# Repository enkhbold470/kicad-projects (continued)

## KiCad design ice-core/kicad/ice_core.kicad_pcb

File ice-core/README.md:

# Ice Core

A 6-layer iCE40UP5K FPGA board with 8 MB PSRAM and three Pmods, programmed and clocked over USB-C by an RP2040.

| Layers | Size | Parts | Nets | Connections routed | Vias | ERC errors | DRC errors / unconnected / parity |
|---|---|---|---|---|---|---|---|
| 6 | 80 x 60 mm | 78 | 73 | 234 -> 0 open | 180 | 0 | 0 / 0 / 0 |

**Not fabricated, assembled or powered.** Every number on this page is measured by KiCad 10 on the files in this folder; the full measurements are in [`report.json`](report.json).

| | |
|---|---|
| KiCad project | [`kicad/`](kicad/) |
| Gerbers, BOM, CPL, STEP, schematic PDF | [`fab/`](fab/) |
| Renders | [top](media/top.png), [bottom](media/bottom.png) |
| Design process, every step as KiCad rendered it | [`media/design-process.mp4`](media/design-process.mp4) |

Ice Core is an FPGA board: a Lattice iCE40UP5K with 8 MB of QSPI PSRAM and three
Pmod host ports, programmed and clocked over USB-C by an RP2040, on 80 x 60 mm of
6-layer board. It was designed with the HeyPCB method on KiCad 10 (the headless
heypcb-kicad pipeline, routed by Freerouting 2.4.1) from the brief in `board.json`.

**This board has not been fabricated, assembled or powered.** It passes ERC, the
netlist round trip, routing, DRC with schematic parity, DFM and the fab gate in
KiCad 10.0.6, headless, and nothing more. No firmware or gateware for it exists.
Every gate number below is read from `report.json`. The stackup, the vias in the
exposed pads, the pours, part positions, pad nets, via counts and spacing, the
silkscreen and each footprint's 3D model were read from `kicad/ice_core.kicad_pcb`
with KiCad 10.0.6's pcbnew.

## What it is

| | |
|---|---|
| FPGA | Lattice iCE40UP5K-SG48 (QFN-48), booting from a W25Q32JV 4 MB SPI flash in controller mode |
| FPGA memory | AP Memory APS6404L-3SQR-SN, 8 MB QSPI pseudo-SRAM (SOIC-8), on six FPGA I/O |
| MCU | Raspberry Pi RP2040 (QFN-56) with its own W25Q32JV 4 MB QSPI boot flash and the ABM8-272-T3 12 MHz crystal |
| MCU role | USB bridge and FPGA programmer: drives CRESET_B, reads CDONE, owns the configuration SPI, clocks the FPGA from GPOUT0 |
| USB | USB-C receptacle (HRO TYPE-C-31-M-12), 5.1k CC pull-downs, USBLC6-2SC6 ESD clamp, 27 ohm series terminations at the RP2040 |
| 3.3 V | Diodes AP63203WU buck from VBUS, 2 A, 3.9 uH |
| 1.2 V | AP2112K-1.2 LDO from VBUS, so the FPGA core rises before its 3.3 V banks; VCCPLL through a 100 ohm / 4.7 uF / 100 nF filter |
| I/O | three 12-pin Pmod host ports (2x6 right-angle sockets) on the FPGA, 8 signals each |
| UI | common-anode RGB LED on the iCE40's RGB driver; BOOT, RESET (RP2040) and USER (FPGA) buttons; PWR, ACT and DONE LEDs |
| Mechanical | 80 x 60 mm, 2 mm corner radius, four M3 holes (3.2 mm) |
| Stackup | 6 copper layers (below) |

### Connections that firmware and gateware need

RP2040 (pin numbers and names from the KiCad symbol, read back from the run's
netlist):

| RP2040 | pin | net | use |
|---|---|---|---|
| GPIO16 | 27 | CFG_CIPO | SPI0 RX: flash DO and the FPGA's SPI_SI |
| GPIO17 | 28 | CFG_SS | SPI0 CSn: flash /CS and the FPGA's SPI_SS_B (10k pull-up) |
| GPIO18 | 29 | CFG_SCK | SPI0 SCK (10k pull-up) |
| GPIO19 | 30 | CFG_COPI | SPI0 TX: flash DI and the FPGA's SPI_SO |
| GPIO20 | 31 | FPGA_CRESET | CRESET_B (10k pull-up) |
| GPIO21 | 32 | FPGA_CLK | GPOUT0 into the iCE40's global buffer pin 35 (IOT_46b_G0) |
| GPIO22 | 34 | FPGA_CDONE | CDONE (10k pull-up) |
| GPIO24 | 36 | LED_DONE | DONE LED (firmware mirrors CDONE) |
| GPIO25 | 37 | LED_ACT | ACT LED |
| QSPI_* | 51-56 | QSPI_* | boot flash |
| USB_DM / USB_DP | 46 / 47 | via 27 ohm | USB-C |

iCE40UP5K-SG48 (package pin numbers; every one except RGB0-2 is an `IO*` pin of
the KiCad symbol):

| function | pins |
|---|---|
| PSRAM CE#, SCLK, SIO0, SIO1, SIO2, SIO3 | 3, 4, 6, 9, 10, 11 |
| Pmod A pins 1-4 / 7-10 | 2, 47, 45, 43 / 48, 46, 44, 42 |
| Pmod B pins 1-4 / 7-10 | 25, 21, 19, 13 / 26, 23, 20, 18 |
| Pmod C pins 1-4 / 7-10 | 38, 36, 32, 28 / 37, 34, 31, 27 |
| clock in (from RP2040 GPOUT0) | 35 (G0) |
| USER button (to GND, enable the pull-up in gateware) | 12 |
| RGB0 / RGB1 / RGB2 | 39 red / 40 green / 41 blue cathode |
| configuration SPI SO / SCK / SS / SI | 14 / 15 / 16 / 17 |

The pin plan: the symbol has 36 `IO*` pins, 4 of them the configuration SPI, which
leaves 32 general I/O, and this board uses all 32. Each Pmod takes the I/O on the
side of the FPGA it faces and its missing pins from the next corner
counter-clockwise (Pmod B from the bottom of the right side, Pmod C from the right
end of the top, Pmod A from the top of the left side), so no Pmod crosses the
configuration SPI at the bottom-left corner. An earlier plan crossed it with Pmod B
and left PB8 open at pin 11. Pmod order along each connector follows the pin order
along the FPGA's edge.

Pmod pin numbers are Digilent's (Pmod Interface Specification 1.1.0, Figure 5).
On KiCad's `PinSocket_2x06_P2.54mm_Horizontal` they land as Pmod pin 1 -> pad 11,
2 -> 9, 3 -> 7, 4 -> 5, 5 (GND) -> 3, 6 (3V3) -> 1, 7 -> 12, 8 -> 10, 9 -> 8,
10 -> 6, 11 (GND) -> 4, 12 (3V3) -> 2: the footprint's square pad 1 is Pmod pin 6.

## Stackup

pcbnew reads 6 copper layers and a 1.6 mm board from the board file. The file holds
no stackup section, so this is KiCad's default 6-layer stackup, not a fab's: choose
the fab's own 6-layer stackup when ordering. pcbnew's stackup object is not
scriptable in KiCad 10.0.6, so the layer thicknesses below come from the gerber job
file (`ice_core-job.gbrjob` in `fab/ice_core_gerbers.zip`). Nothing on this board
is impedance controlled (USB runs at Full Speed).

| layer | role while routing | pour after routing | filled as | copper |
|---|---|---|---|---|
| F.Cu | signal | GND | 12 pieces | 0.035 mm |
| In1.Cu | GND plane | GND | 1 piece | 0.035 mm |
| In2.Cu | signal | GND | 2 pieces | 0.035 mm |
| In3.Cu | power plane | 3V3, zone priority 1 | 1 piece | 0.035 mm |
| In4.Cu | GND plane | GND | 1 piece | 0.035 mm |
| B.Cu | signal | GND | 1 piece | 0.035 mm |

In3.Cu is `auto` in the brief: the supply rail with at least 1.5x the pins of the
next one. In this run's netlist 3V3 has 54 pins and no other supply more than 12
(VBUS). Five FR4 dielectrics of 0.274 mm, 1.6 mm overall.

Why this plan: every routed layer sits next to a plane (F.Cu over In1, In2 between
In1 and In3, B.Cu over In4), so every signal has its return path beside it, and
In3/In4 are a tightly coupled power/ground pair. Each of the three planes fills as
one piece. The pieces are counted on the fill stored in the board file. The silk
stage removed 8 stitching vias after that fill, and refilling a copy of the board
gave the same counts on every layer. The price is routing room: Freerouting routes
on F.Cu, In2.Cu and B.Cu only, the same three layers as on a 4-layer board.

## Measured gates

One full run with media, 2026-10-01: KiCad 10.0.6 (from the DRC report),
Freerouting 2.4.1 (from its log). The Specctra export carried the brief's 0.5 mm
hole-to-hole minimum to Freerouting as a 0.3 mm `via_via` clearance
(`viaViaClearance_mm` in the report: 0.5 mm + 0.3 mm drill - 0.5 mm via).

| gate | measured |
|---|---|
| Compose | 78 parts, 73 nets, 3 no-connects (J1.A8, J1.B8, U3.4) |
| Part binding | 74 bound, 0 unsourced, 0 conflicts; H1-H4 not in the BOM; 17 Extended part numbers, $51.0 estimated JLC Extended fees |
| ERC | 0 errors, 0 warnings |
| Netlist round trip | identical, 73 nets |
| Route | 234 -> 0 open. Fanout solve kept: 0 open, DRC score 0, 101 vias. Fanout-off solve: 2 open (PSRAM_CS, U4_RP_DM), and the last mile closed neither (U4_RP_DM hit its 400,000-expansion search cap, PSRAM_CS had no path). 2 locked vias in exposed pads (U4.57, U6.49). 839 tracks, 2034.8 mm (F.Cu 1180.9, In2.Cu 644.1, B.Cu 209.8) |
| Pours | GND on F.Cu, B.Cu, In1.Cu, In4.Cu, In2.Cu; 3V3 on In3.Cu; 87 stitching vias, 0 island-repair vias; 0 open after the pours, after stitching and at the end; 188 vias after the pours |
| Silkscreen | 11 of 11 words in place of designators; 55 designators seated, 12 hidden where nothing fit; all 4 title lines placed, on the back; 8 GND stitching vias displaced under text; 90 footprint silk items clipped at the board edge (29 on each Pmod socket J2-J4, 3 on the USB-C J1) |
| DRC (fresh, schematic parity) | 0 errors, 0 unconnected, 0 parity; 4 warnings, all `lib_footprint_mismatch`, on J1-J4, the four footprints whose silk was clipped; no repairs |
| DFM (`jlcpcb_6layer`) | 0 errors, 1 warning: stock footprint silk down to 0.10 mm (292 items), printed at the fab's 0.15 mm |
| Fab | ready, no blockers; 6 copper gerbers (F, In1, In2, In3, In4, B) and a gerber job with LayerNumber 6 and a 1.6 mm board; drill, BOM, CPL (6 rotations corrected), schematic PDF, STEP |
| Media | all ran: 63 3D frames, then the raytraced renders and the design-process video (216 frames; 150.0 s at 1920 x 1080, measured with ffprobe) |

Vias, measured on the finished board: 180 in all. 101 are routed vias at 0.5/0.3 mm,
2 of them the locked vias in the exposed pads. 79 are stitching vias at 0.6/0.3 mm:
87 laid by the pour stage, less the 8 the silkscreen displaced. The closest two via
holes are 0.507 mm apart (PB10 and PB3), and no pair is under the 0.5 mm minimum.
DRC reports no `hole_to_hole` rows.

## Silkscreen

The front carries a word instead of a designator on the 11 parts a user plugs into,
presses or reads: USB, PMOD A, PMOD B, PMOD C, BOOT, RST, USER, PWR, ACT, DONE and
RGB.

The board's name is on the back: all four title lines ("Ice Core", "iCE40UP5K +
RP2040, 6 layers", "rev A  heypcb-kicad", "pure KiCad 10 + Freerouting"), placed as
one block. The brief asks for the block on the board's centre line, 22 mm from the
top edge. That spot was not free, so the block landed 9 mm left and 3 mm down, at
x 19.9-42.1 mm and y 23.5-32.9 mm from the board's top-left corner, behind the
RP2040's right side and the PSRAM. The previous full run, the one this README
described before, placed none of the four lines, because the 5 mm stitching-via
grid left no gap long enough. Text may now displace a GND stitching via. This run
displaced 8: 4 under the title and 4 under the ACT, BOOT, USER and PMOD A words.

## Files

- `board.json`: the brief the pipeline built everything here from.
- `report.json`: the run's gate report, the source of every number above.
- `kicad/`: `ice_core.kicad_pro`, `ice_core.kicad_sch`, `ice_core.kicad_pcb`
  (routed and poured) and `models/`, the two generated 3D envelopes (D1 and J1,
  below).
- `fab/ice_core_gerbers.zip`: 13 layer gerbers, the gerber job, the drill file
  and the drill map.
- `fab/ice_core_bom.csv`, `fab/ice_core_cpl_jlc.csv` (JLC placement, rotations
  corrected), `fab/ice_core_pos.csv` (KiCad placement),
  `fab/ice_core_schematic.pdf`, `fab/ice_core.step` (72 bodies; none for D1, J1
  or the mounting holes).
- `media/`: `hero.png`, `top.png`, `bottom.png` and the design-process video
  (`design-process.mp4`, `design-process.gif`).

## 3D models

KiCad 10.0.6 installs no 3D model for three of the footprints this board uses,
so the pipeline gives each a stand-in (read from each footprint's model path on
the board):

- **U6, the iCE40** (`QFN-48-1EP_7x7mm_P0.5mm_EP5.6x5.6mm`) uses the library's
  `QFN-48-1EP_7x7mm_P0.5mm_EP5.15x5.15mm.step`. It is the same 7 x 7 mm body
  with the same 48 pins. Only the exposed pad differs, and the body hides it.
  `fab/ice_core.step` carries this body.
- **D1, the RGB LED** (`LED_Avago_PLCC4_3.2x2.8mm_CW`) is a simplified envelope
  that the pipeline generates (`kicad/models/led_plcc4_3.2x2.8.wrl`): a white
  3.2 x 2.8 mm body with a clear lens and a dark mark at the pad-1 corner. Its
  1.9 mm height is an assumption. It is not the TuoZhan part's model.
- **J1, the USB-C receptacle** is also a generated envelope
  (`kicad/models/usb_c_hro_type-c-31-m-12.wrl`).

Both envelopes are VRML files. They show in the renders, but `fab/ice_core.step`
has no body for D1 or J1.

## Parts that are not what the request named

- **iCE40UP5K-SG48I (LCSC C2678152), the tray part**, on KiCad's
  `FPGA_Lattice:ICE40UP5K-SG48ITR` symbol (tape and reel): same die, same QFN-48.
  LCSC stocks only the tray part.
- **W25Q32JVSSIQ (C179173) as the RP2040's boot flash**, where Raspberry Pi's
  minimal design uses a W25Q128JVS. The RP2040's `boot2_w25q080` second stage
  drives any W25Q part in quad-I/O mode; this one holds 4 MB. It is the same
  part as the FPGA's configuration flash.
- **RGB LED: TuoZhan S4-3528RGBTA-A (C2827321)** on KiCad's
  `LED_Avago_PLCC4_3.2x2.8mm_CW` footprint with the `Device:LED_BGRA` symbol.
  KiCad's Broadcom ASMB-MTB0/MTB1 symbols carry their own footprint, but LCSC
  lists neither part. The part's data sheet numbers its pins 1 blue cathode,
  2 anode, 3 green cathode, 4 red cathode. With its pin 1 on pad 1, the footprint's
  pads 1-4 carry blue, green and red cathode and the anode (on the board: LED_B,
  LED_G, LED_R, 3V3), which is `Device:LED_BGRA`. The part's own pins 2-4 are not
  the pad numbers.
- **10k resistors: FRC0603F1002TS (C2906982, Extended)** instead of the Basic
  C25804 the pinned table offers: that one had 0 stock and is no longer in the
  live catalogue (2026-09-30).

Part numbers come from heypcb-kicad's pinned LCSC table. Of the 28 distinct LCSC
numbers in `fab/ice_core_bom.csv`, 14 carry a live lookup dated 2026-09-30 and 14
older snapshots (2026-06-23 to 2026-07-03), so check stock when ordering. The
APS6404L-3SQR-SN (C5333729) had 41 in stock at its lookup.

## Check before ordering

1. **It has never been built.** Order one panel, assemble one board, and bring
   it up rail by rail (VBUS, 3.3 V, 1.2 V) before trusting anything else.
2. **Stackup.** The board file states none, so the gerber job carries KiCad's
   default. Replace it with the fab's 6-layer stackup.
3. **Vias in the exposed pads.** One locked 0.5/0.3 mm GND via sits at the centre
   of each exposed pad: the RP2040's (U4.57, 3.2 x 3.2 mm) and the iCE40's
   (U6.49, 5.6 x 5.6 mm). The board asks for no filling and no capping. On top
   each via lies inside the pad's solder-mask opening, an open hole, and the
   paste windows (4 on U4, 16 on U6) leave it uncovered. Ask for filled and capped
   vias, or expect solder to wick into them.
4. **RGB LED orientation and land pattern.** The S4-3528RGBTA-A's recommended
   pads (1.8 x 0.8 mm, 1.6 mm apart, from its data sheet) lie only roughly inside
   the Avago footprint's (1.5 x 1.1 mm at 3.0 x 1.5 mm pitch, measured on D1).
   Check pin 1 and the paste in the assembler's preview.
5. **VCCPLL filter.** The 100 nF (C27) sits at pin 29: its VCCPLL pad centre is
   1.84 mm from the pin's. The 100 ohm (R8) and the 4.7 uF (C26) sit below-right of the
   FPGA, at (57.25, 38.50) mm and (60.50, 39.00) mm from the board's top-left,
   8.6 and 10.9 mm from pin 29, out of Pmod C's escape. U6_VCCPLL runs 15.8 mm
   of track (F.Cu 7.0, In2.Cu 8.8) through 2 vias. Move them closer if you can
   route it.
6. **VPP_2V5 runs from 3.3 V** (pin 24 is on the 3V3 net). Fine for booting from
   flash and for the RGB driver; never program the iCE40's NVCM from this rail.
7. **Firmware has to do the board's job**: start GPOUT0 (the FPGA's only clock),
   hold CRESET_B low while it writes the configuration flash, then release the
   SPI pins (tri-state) before releasing CRESET_B, since the FPGA reads the same
   flash as an SPI controller.
8. **Extended parts**: 17 Extended part numbers, about $51 in JLC's per-part
   Extended fees at the report's estimate.

## Reproduce

From the heypcb-kicad repository:

```bash
./run.sh --board boards/ice_core              # with the 3D renders and the video
./run.sh --board boards/ice_core --no-media   # the gates only
```

Placement walks parts in reference order and the Specctra file is written in a
content-only order, so the brief is meant to route the same way every time. This
README reports one run. The previous full run, made before the silkscreen and
3D-model changes, reported the same route: 234 -> 0 open, 101 vias, 839 tracks and
2034.8 mm. An earlier run without media also gave 234 -> 0 open with 101 vias. The
boards were not compared track by track.

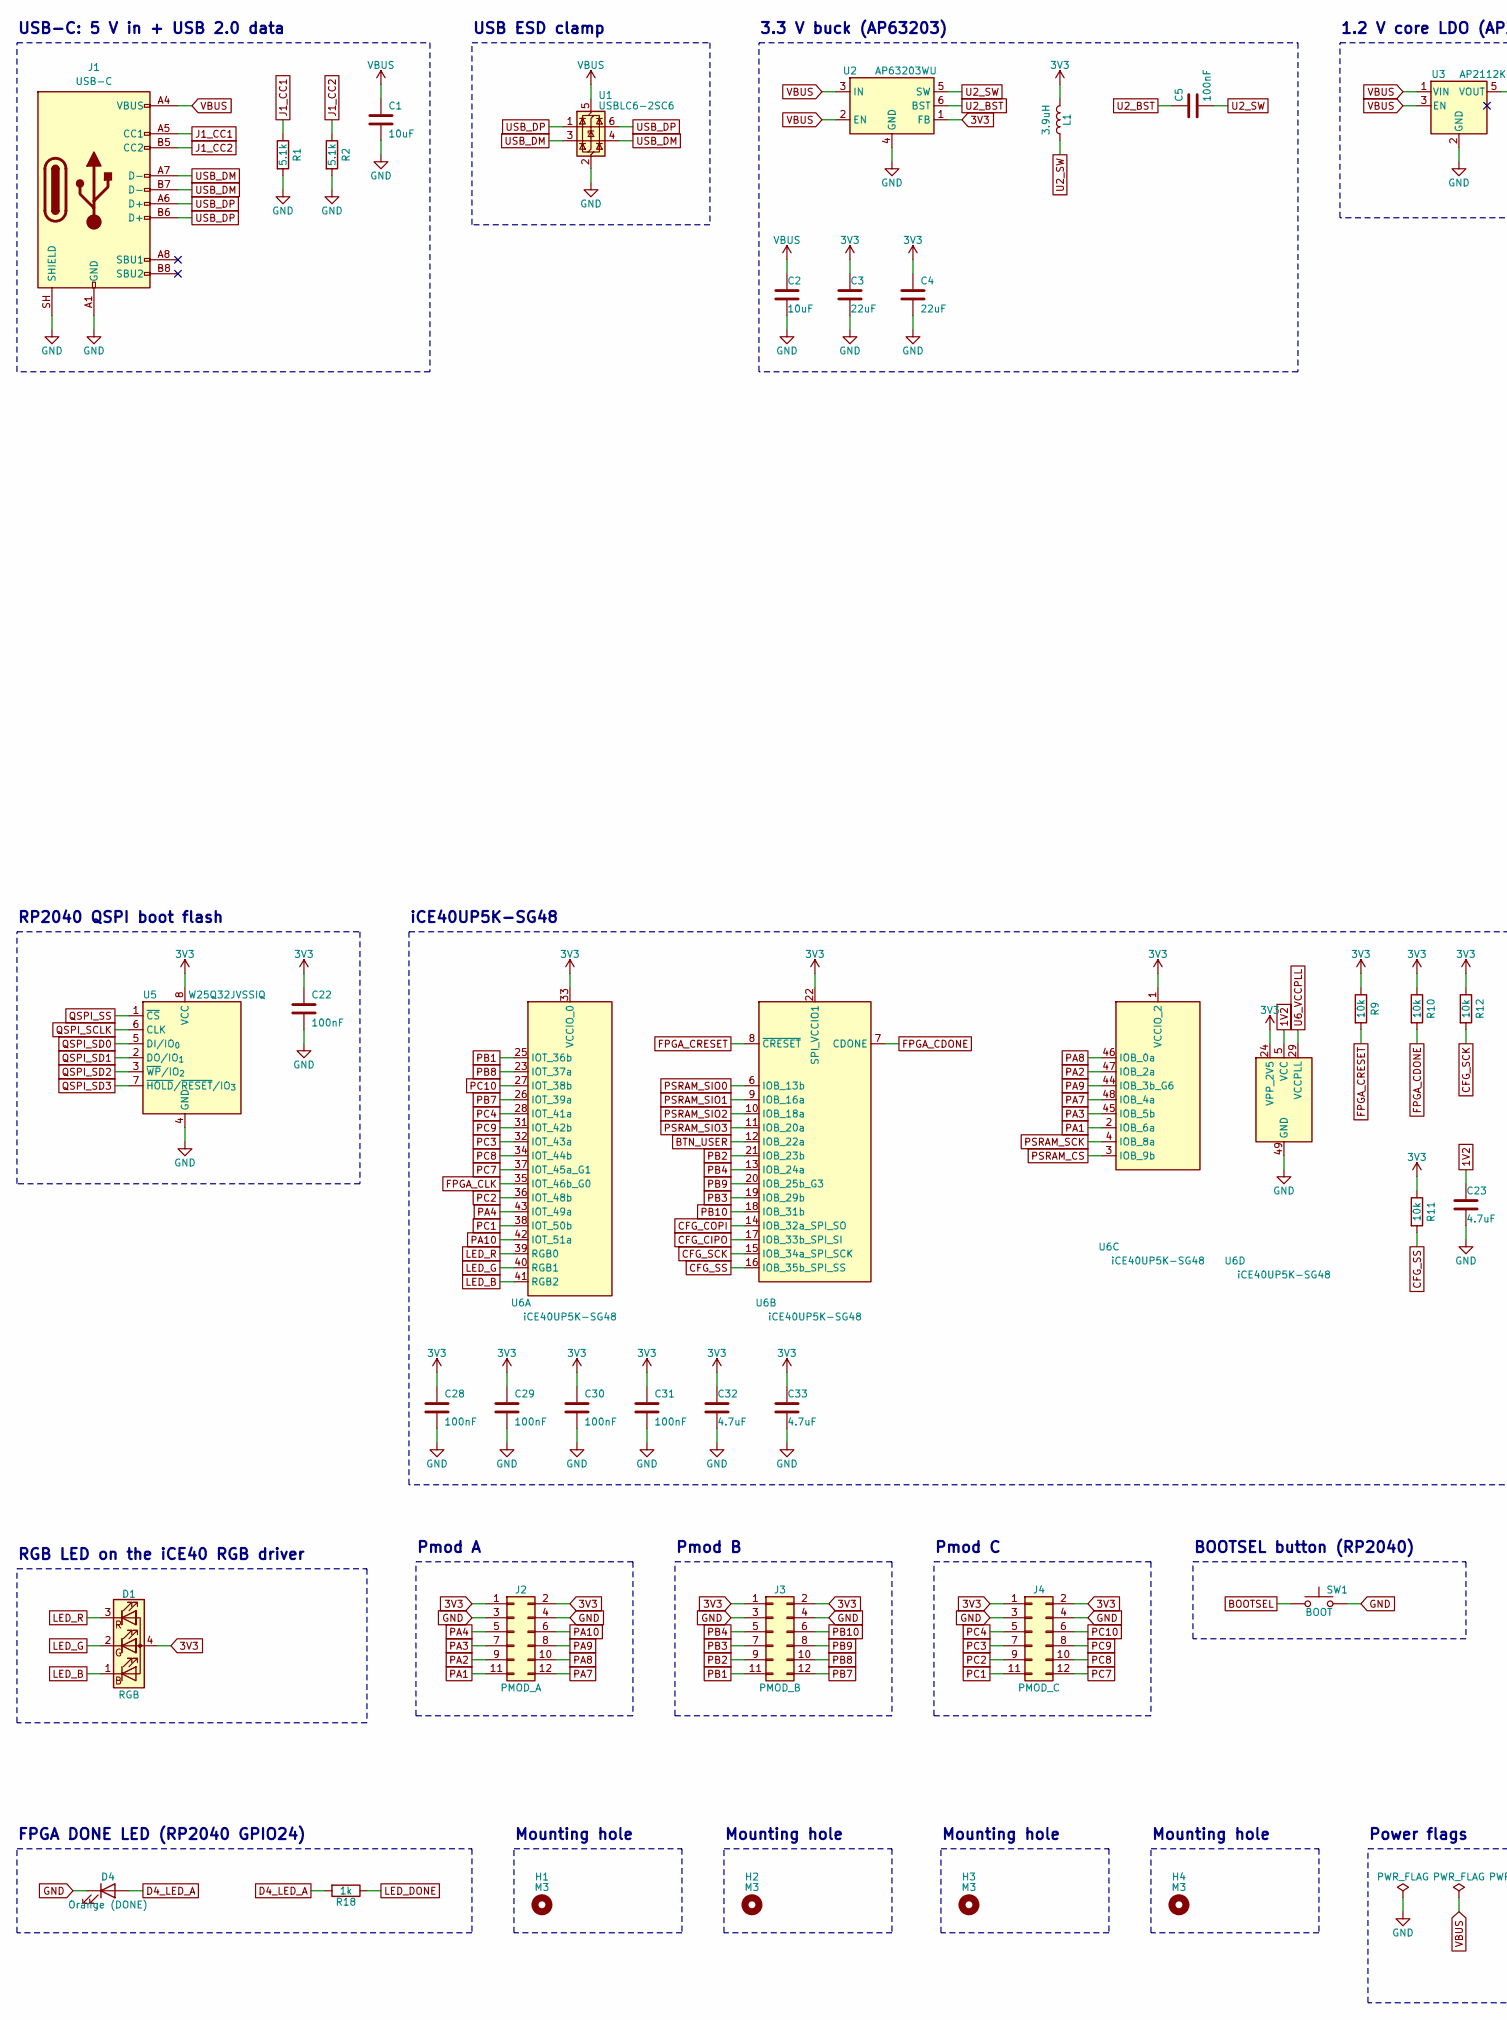
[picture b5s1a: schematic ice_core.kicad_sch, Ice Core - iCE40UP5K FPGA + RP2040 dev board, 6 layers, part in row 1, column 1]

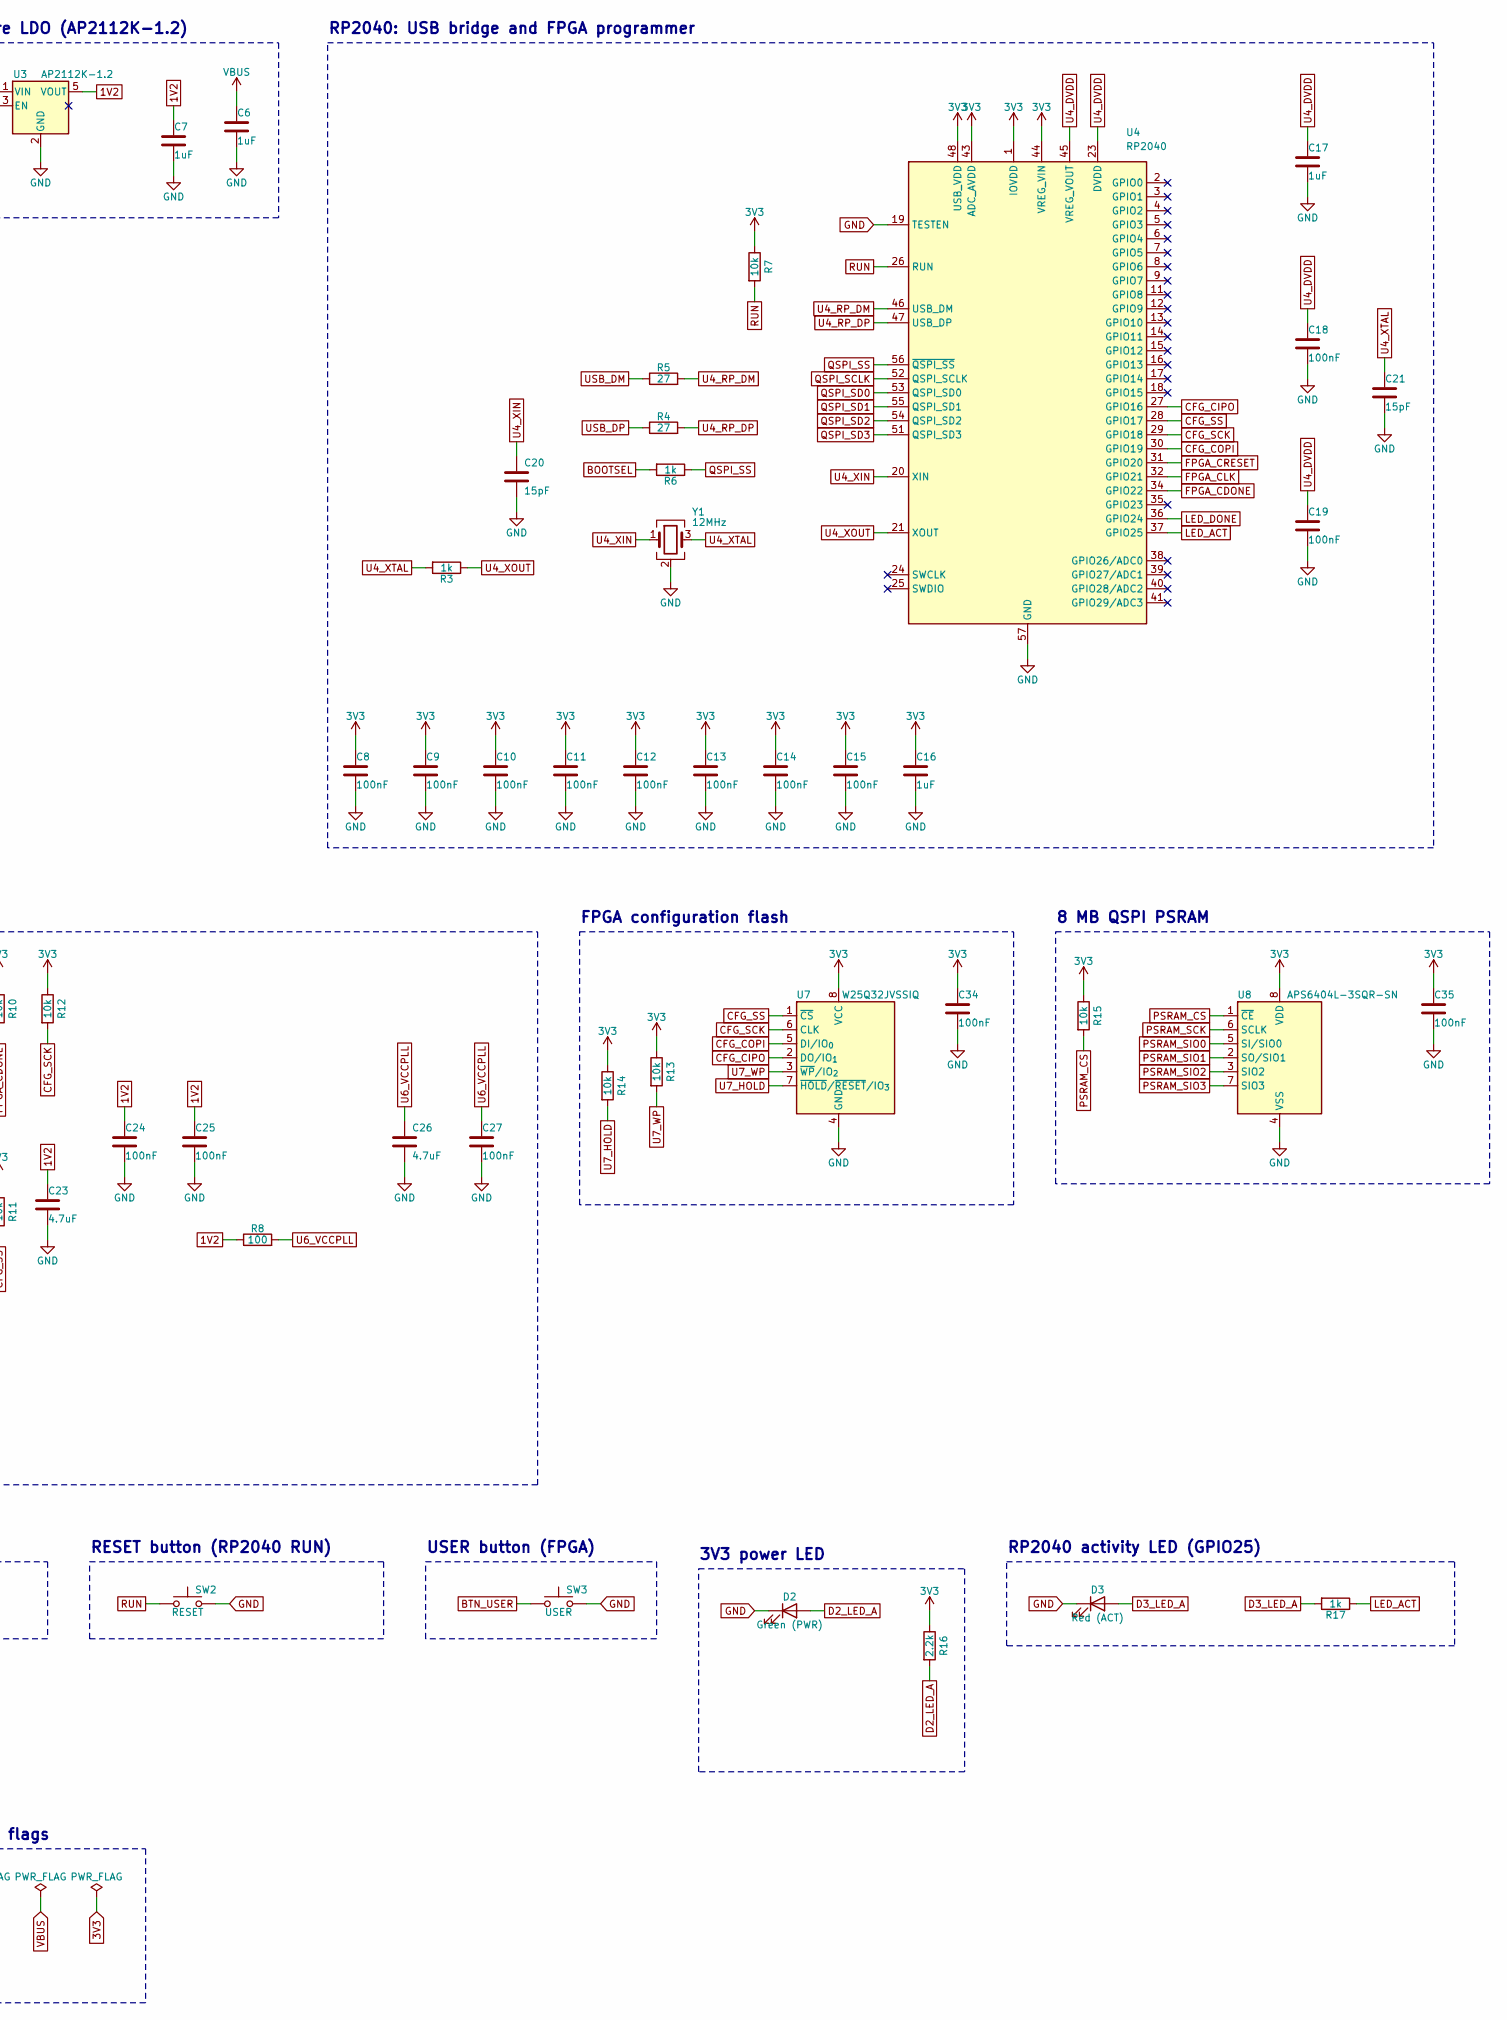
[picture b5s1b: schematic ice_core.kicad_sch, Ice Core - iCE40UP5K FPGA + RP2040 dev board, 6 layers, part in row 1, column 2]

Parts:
C1, C2: 10uF; C_0805_2012Metric; MPN CL21A106KAYNNNE; LCSC C15850
C3, C4: 22uF; C_0805_2012Metric; MPN CL21A226MAQNNNE; LCSC C45783
C5, C8, C9, C10, C11, C12, C13, C14, C15, C18, C19, C22, C24, C25, C27, C28, C29, C30, C31, C34, C35: 100nF; C_0603_1608Metric; MPN CC0603KRX7R9BB104; LCSC C14663
C6, C7, C16, C17: 1uF; C_0603_1608Metric; MPN CL10A105KB8NNNC; LCSC C15849
C20, C21: 15pF; C_0603_1608Metric; MPN CL10C150JB8NNNC; LCSC C1644
C23, C26, C32, C33: 4.7uF; C_0805_2012Metric; MPN CL21A475KAQNNNE; LCSC C1779
D1: RGB; LED_Avago_PLCC4_3.2x2.8mm_CW; MPN S4-3528RGBTA-A; LCSC C2827321
D2: Green (PWR); LED_0603_1608Metric; MPN KT-0603G; LCSC C12624
D3: Red (ACT); LED_0603_1608Metric; MPN KT-0603R; LCSC C2286
D4: Orange (DONE); LED_0603_1608Metric; MPN XL-1608UOC-06; LCSC C965800
H1, H2, H3, H4: M3; MountingHole_3.2mm_M3
J1: USB-C; USB_C_Receptacle_HRO_TYPE-C-31-M-12; MPN TYPE-C-31-M-12; LCSC C165948
J2: PMOD_A; PinSocket_2x06_P2.54mm_Horizontal; MPN PM254-2-06-W-8.5; LCSC C2897426
J3: PMOD_B; PinSocket_2x06_P2.54mm_Horizontal; MPN PM254-2-06-W-8.5; LCSC C2897426
J4: PMOD_C; PinSocket_2x06_P2.54mm_Horizontal; MPN PM254-2-06-W-8.5; LCSC C2897426
L1: 3.9uH; L_Sunlord_SWPA4030S; MPN SWPA4030S3R9MT; LCSC C96899
R1, R2: 5.1k; R_0402_1005Metric; MPN 0402WGF5101TCE; LCSC C25905
R3, R6, R17, R18: 1k; R_0603_1608Metric; MPN 0603WAF1001T5E; LCSC C21190
R4, R5: 27; R_0603_1608Metric; MPN 0603WAF270JT5E; LCSC C25190
R7, R9, R10, R11, R12, R13, R14, R15: 10k; R_0603_1608Metric; MPN FRC0603F1002TS; LCSC C2906982
R8: 100; R_0603_1608Metric; MPN 0603WAF1000T5E; LCSC C22775
R16: 2.2k; R_0603_1608Metric; MPN 0603WAF2201T5E; LCSC C4190
SW1: BOOT; SW_SPST_PTS810; MPN PTS810SJM250SMTRLFS; LCSC C116501
SW2: RESET; SW_SPST_PTS810; MPN PTS810SJM250SMTRLFS; LCSC C116501
SW3: USER; SW_SPST_PTS810; MPN PTS810SJM250SMTRLFS; LCSC C116501
U1: USBLC6-2SC6; SOT-23-6; MPN USBLC6-2SC6; LCSC C7519
U2: AP63203WU; TSOT-23-6; MPN AP63203WU-7; LCSC C780769
U3: AP2112K-1.2; SOT-23-5; MPN AP2112K-1.2TRG1; LCSC C460310
U4: RP2040; QFN-56-1EP_7x7mm_P0.4mm_EP3.2x3.2mm; MPN RP2040; LCSC C2040
U5, U7: W25Q32JVSSIQ; SOIC-8_5.3x5.3mm_P1.27mm; MPN W25Q32JVSSIQ; LCSC C179173
U6: iCE40UP5K-SG48; QFN-48-1EP_7x7mm_P0.5mm_EP5.6x5.6mm; MPN ICE40UP5K-SG48I; LCSC C2678152
U8: APS6404L-3SQR-SN; SOIC-8_3.9x4.9mm_P1.27mm; MPN APS6404L-3SQR-SN; LCSC C5333729
Y1: 12MHz; Crystal_SMD_3225-4Pin_3.2x2.5mm; MPN ABM8-272-T3; LCSC C20625731

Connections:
1V2: C7.1, C23.1, C24.1, C25.1, R8.1, U3.5 (VOUT), U6.5 (VCC), U6.30 (VCC)
3V3: C3.1, C4.1, C8.1, C9.1, C10.1, C11.1, C12.1, C13.1, C14.1, C15.1, C16.1, C22.1, C28.1, C29.1, C30.1, C31.1, C32.1, C33.1, C34.1, C35.1, D1.4 (A), J2.1, J2.2, J3.1, J3.2, J4.1, J4.2, L1.2, R7.1, R9.1, R10.1, R11.1, R12.1, R13.1, R14.1, R15.1, R16.1, U2.1 (FB), U4.1 (IOVDD), U4.10 (IOVDD), U4.22 (IOVDD), U4.33 (IOVDD), U4.42 (IOVDD), U4.43 (ADC_AVDD), U4.44 (VREG_VIN), U4.48 (USB_VDD), U4.49 (IOVDD), U5.8 (VCC), U6.1 (VCCIO_2), U6.22 (SPI_VCCIO1), U6.24 (VPP_2V5), U6.33 (VCCIO_0), U7.8 (VCC), U8.8 (VDD)
BOOTSEL: R6.2, SW1.1
BTN_USER: SW3.1, U6.12 (IOB_22a)
CFG_CIPO: U4.27 (GPIO16), U6.17 (IOB_33b_SPI_SI), U7.2 (DO/IO_{1})
CFG_COPI: U4.30 (GPIO19), U6.14 (IOB_32a_SPI_SO), U7.5 (DI/IO_{0})
CFG_SCK: R12.2, U4.29 (GPIO18), U6.15 (IOB_34a_SPI_SCK), U7.6 (CLK)
CFG_SS: R11.2, U4.28 (GPIO17), U6.16 (IOB_35b_SPI_SS), U7.1 (~CS)
D2_LED_A: D2.2 (A), R16.2
D3_LED_A: D3.2 (A), R17.2
D4_LED_A: D4.2 (A), R18.2
FPGA_CDONE: R10.2, U4.34 (GPIO22), U6.7 (CDONE)
FPGA_CLK: U4.32 (GPIO21), U6.35 (IOT_46b_G0)
FPGA_CRESET: R9.2, U4.31 (GPIO20), U6.8 (~CRESET)
GND: C1.2, C2.2, C3.2, C4.2, C6.2, C7.2, C8.2, C9.2, C10.2, C11.2, C12.2, C13.2, C14.2, C15.2, C16.2, C17.2, C18.2, C19.2, C20.2, C21.2, C22.2, C23.2, C24.2, C25.2, C26.2, C27.2, C28.2, C29.2, C30.2, C31.2, C32.2, C33.2, C34.2, C35.2, D2.1 (K), D3.1 (K), D4.1 (K), J1.A1 (GND), J1.A12 (GND), J1.B1 (GND), J1.B12 (GND), J1.SH (SHIELD), J2.3, J2.4, J3.3, J3.4, J4.3, J4.4, R1.2, R2.2, SW1.2, SW2.2, SW3.2, U1.2 (GND), U2.4 (GND), U3.2 (GND), U4.19 (TESTEN), U4.57 (GND), U5.4 (GND), U6.49 (GND), U7.4 (GND), U8.4 (VSS), Y1.2 (G), Y1.4 (G)
J1_CC1: J1.A5 (CC1), R1.1
J1_CC2: J1.B5 (CC2), R2.1
LED_ACT: R17.1, U4.37 (GPIO25)
LED_B: D1.1 (BK), U6.41 (RGB2)
LED_DONE: R18.1, U4.36 (GPIO24)
LED_G: D1.2 (GK), U6.40 (RGB1)
LED_R: D1.3 (RK), U6.39 (RGB0)
PA1: J2.11, U6.2 (IOB_6a)
PA2: J2.9, U6.47 (IOB_2a)
PA3: J2.7, U6.45 (IOB_5b)
PA4: J2.5, U6.43 (IOT_49a)
PA7: J2.12, U6.48 (IOB_4a)
PA8: J2.10, U6.46 (IOB_0a)
PA9: J2.8, U6.44 (IOB_3b_G6)
PA10: J2.6, U6.42 (IOT_51a)
PB1: J3.11, U6.25 (IOT_36b)
PB2: J3.9, U6.21 (IOB_23b)
PB3: J3.7, U6.19 (IOB_29b)
PB4: J3.5, U6.13 (IOB_24a)
PB7: J3.12, U6.26 (IOT_39a)
PB8: J3.10, U6.23 (IOT_37a)
PB9: J3.8, U6.20 (IOB_25b_G3)
PB10: J3.6, U6.18 (IOB_31b)
PC1: J4.11, U6.38 (IOT_50b)
PC2: J4.9, U6.36 (IOT_48b)
PC3: J4.7, U6.32 (IOT_43a)
PC4: J4.5, U6.28 (IOT_41a)
PC7: J4.12, U6.37 (IOT_45a_G1)
PC8: J4.10, U6.34 (IOT_44b)
PC9: J4.8, U6.31 (IOT_42b)
PC10: J4.6, U6.27 (IOT_38b)
PSRAM_CS: R15.2, U6.3 (IOB_9b), U8.1 (~CE)
PSRAM_SCK: U6.4 (IOB_8a), U8.6 (SCLK)
PSRAM_SIO0: U6.6 (IOB_13b), U8.5 (SI/SIO0)
PSRAM_SIO1: U6.9 (IOB_16a), U8.2 (SO/SIO1)
PSRAM_SIO2: U6.10 (IOB_18a), U8.3 (SIO2)
PSRAM_SIO3: U6.11 (IOB_20a), U8.7 (SIO3)
QSPI_SCLK: U4.52 (QSPI_SCLK), U5.6 (CLK)
QSPI_SD0: U4.53 (QSPI_SD0), U5.5 (DI/IO_{0})
QSPI_SD1: U4.55 (QSPI_SD1), U5.2 (DO/IO_{1})
QSPI_SD2: U4.54 (QSPI_SD2), U5.3 (~WP/IO_{2})
QSPI_SD3: U4.51 (QSPI_SD3), U5.7 (~HOLD/~RESET/IO_{3})
QSPI_SS: R6.1, U4.56 (~QSPI_SS), U5.1 (~CS)
RUN: R7.2, SW2.1, U4.26 (RUN)
U2_BST: C5.1, U2.6 (BST)
U2_SW: C5.2, L1.1, U2.5 (SW)
U4_DVDD: C17.1, C18.1, C19.1, U4.23 (DVDD), U4.45 (VREG_VOUT), U4.50 (DVDD)
U4_RP_DM: R5.2, U4.46 (USB_DM)
U4_RP_DP: R4.2, U4.47 (USB_DP)
U4_XIN: C20.1, U4.20 (XIN), Y1.1
U4_XOUT: R3.1, U4.21 (XOUT)
U4_XTAL: C21.1, R3.2, Y1.3
U6_VCCPLL: C26.1, C27.1, R8.2, U6.29 (VCCPLL)
U7_HOLD: R14.2, U7.7 (~HOLD/~RESET/IO_{3})
U7_WP: R13.2, U7.3 (~WP/IO_{2})
USB_DM: J1.A7 (D-), J1.B7 (D-), R5.1, U1.3 (I/O2), U1.4 (I/O2)
USB_DP: J1.A6 (D+), J1.B6 (D+), R4.1, U1.1 (I/O1), U1.6 (I/O1)
VBUS: C1.1, C2.1, C6.1, J1.A4 (VBUS), J1.A9 (VBUS), J1.B4 (VBUS), J1.B9 (VBUS), U1.5 (VBUS), U2.2 (EN), U2.3 (IN), U3.1 (VIN), U3.3 (EN)

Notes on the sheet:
USB-C: 5 V in + USB 2.0 data
USB ESD clamp
3.3 V buck (AP63203)
1.2 V core LDO (AP2112K-1.2)
RP2040: USB bridge and FPGA programmer
RP2040 QSPI boot flash
iCE40UP5K-SG48
FPGA configuration flash
8 MB QSPI PSRAM
RGB LED on the iCE40 RGB driver
Pmod A
Pmod B
Pmod C
BOOTSEL button (RP2040)
RESET button (RP2040 RUN)
USER button (FPGA)
3V3 power LED
RP2040 activity LED (GPIO25)
FPGA DONE LED (RP2040 GPIO24)
Mounting hole
Power flags

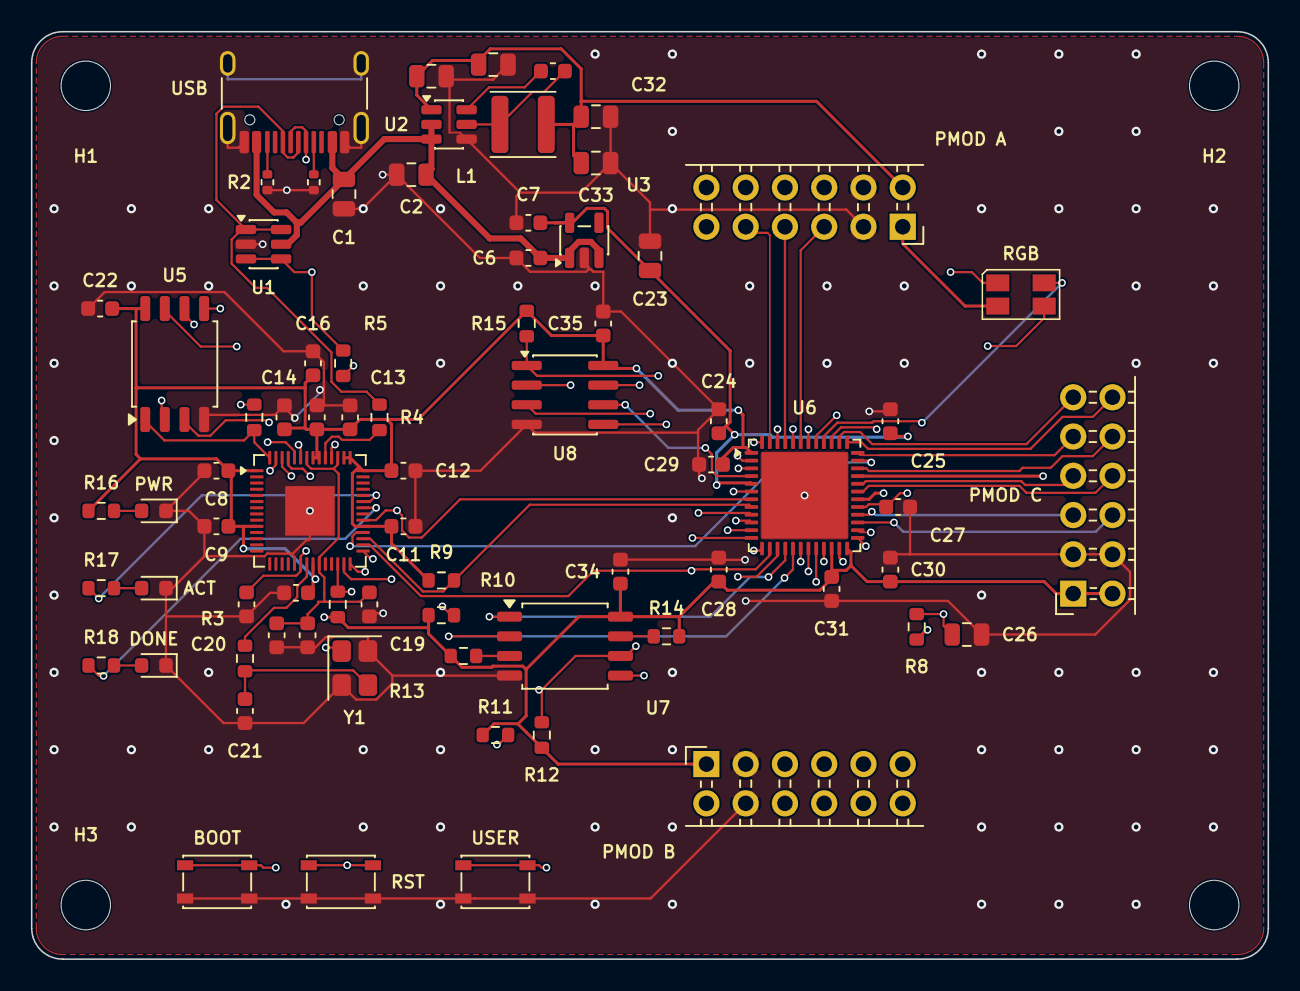
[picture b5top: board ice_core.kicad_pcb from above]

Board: 6 copper layers, 80.0 x 60.0 mm, 78 parts (0 on the bottom side), 73 nets.

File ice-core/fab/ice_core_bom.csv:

"Reference","Value","Footprint","MPN","LCSC","Qty"
"C1,C2","10uF","Capacitor_SMD:C_0805_2012Metric","CL21A106KAYNNNE","C15850","2"
"C3,C4","22uF","Capacitor_SMD:C_0805_2012Metric","CL21A226MAQNNNE","C45783","2"
"C5,C8,C9,C10,C11,C12,C13,C14,C15,C18,C19,C22,C24,C25,C27,C28,C29,C30,C31,C34,C35","100nF","Capacitor_SMD:C_0603_1608Metric","CC0603KRX7R9BB104","C14663","21"
"C6,C7,C16,C17","1uF","Capacitor_SMD:C_0603_1608Metric","CL10A105KB8NNNC","C15849","4"
"C20,C21","15pF","Capacitor_SMD:C_0603_1608Metric","CL10C150JB8NNNC","C1644","2"
"C23,C26,C32,C33","4.7uF","Capacitor_SMD:C_0805_2012Metric","CL21A475KAQNNNE","C1779","4"
"D1","RGB","LED_SMD:LED_Avago_PLCC4_3.2x2.8mm_CW","S4-3528RGBTA-A","C2827321","1"
"D2","Green (PWR)","LED_SMD:LED_0603_1608Metric","KT-0603G","C12624","1"
"D3","Red (ACT)","LED_SMD:LED_0603_1608Metric","KT-0603R","C2286","1"
"D4","Orange (DONE)","LED_SMD:LED_0603_1608Metric","XL-1608UOC-06","C965800","1"
"J1","USB-C","Connector_USB:USB_C_Receptacle_HRO_TYPE-C-31-M-12","TYPE-C-31-M-12","C165948","1"
"J2","PMOD_A","Connector_PinSocket_2.54mm:PinSocket_2x06_P2.54mm_Horizontal","PM254-2-06-W-8.5","C2897426","1"
"J3","PMOD_B","Connector_PinSocket_2.54mm:PinSocket_2x06_P2.54mm_Horizontal","PM254-2-06-W-8.5","C2897426","1"
"J4","PMOD_C","Connector_PinSocket_2.54mm:PinSocket_2x06_P2.54mm_Horizontal","PM254-2-06-W-8.5","C2897426","1"
"L1","3.9uH","Inductor_SMD:L_Sunlord_SWPA4030S","SWPA4030S3R9MT","C96899","1"
"R1,R2","5.1k","Resistor_SMD:R_0402_1005Metric","0402WGF5101TCE","C25905","2"
"R3,R6,R17,R18","1k","Resistor_SMD:R_0603_1608Metric","0603WAF1001T5E","C21190","4"
"R4,R5","27","Resistor_SMD:R_0603_1608Metric","0603WAF270JT5E","C25190","2"
"R7,R9,R10,R11,R12,R13,R14,R15","10k","Resistor_SMD:R_0603_1608Metric","FRC0603F1002TS","C2906982","8"
"R8","100","Resistor_SMD:R_0603_1608Metric","0603WAF1000T5E","C22775","1"
"R16","2.2k","Resistor_SMD:R_0603_1608Metric","0603WAF2201T5E","C4190","1"
"SW1","BOOT","Button_Switch_SMD:SW_SPST_PTS810","PTS810SJM250SMTRLFS","C116501","1"
"SW2","RESET","Button_Switch_SMD:SW_SPST_PTS810","PTS810SJM250SMTRLFS","C116501","1"
"SW3","USER","Button_Switch_SMD:SW_SPST_PTS810","PTS810SJM250SMTRLFS","C116501","1"
"U1","USBLC6-2SC6","Package_TO_SOT_SMD:SOT-23-6","USBLC6-2SC6","C7519","1"
"U2","AP63203WU","Package_TO_SOT_SMD:TSOT-23-6","AP63203WU-7","C780769","1"
"U3","AP2112K-1.2","Package_TO_SOT_SMD:SOT-23-5","AP2112K-1.2TRG1","C460310","1"
"U4","RP2040","Package_DFN_QFN:QFN-56-1EP_7x7mm_P0.4mm_EP3.2x3.2mm","RP2040","C2040","1"
"U5,U7","W25Q32JVSSIQ","Package_SO:SOIC-8_5.3x5.3mm_P1.27mm","W25Q32JVSSIQ","C179173","2"
"U6","iCE40UP5K-SG48","Package_DFN_QFN:QFN-48-1EP_7x7mm_P0.5mm_EP5.6x5.6mm","ICE40UP5K-SG48I","C2678152","1"
"U8","APS6404L-3SQR-SN","Package_SO:SOIC-8_3.9x4.9mm_P1.27mm","APS6404L-3SQR-SN","C5333729","1"
"Y1","12MHz","Crystal:Crystal_SMD_3225-4Pin_3.2x2.5mm","ABM8-272-T3","C20625731","1"
